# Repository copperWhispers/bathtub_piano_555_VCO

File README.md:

# bathtub_piano_555_VCO
bathtub tune-able analog keyboard based around a 555 timer chip used in PPM configuration.

Story Telling of the journey:
https://youtu.be/zMRLficPjbc

NE555:
https://www.ti.com/lit/ds/symlink/ne555.pdf

KiCAD Schematic and Layout attached.

Also attached a rough notes document which is the doc I wrote into as I designed this circuit, you can see it as an in depth technical version of the journey presented in the video.

References:

Ref1: notes and their frequencies
https://www.idrumtune.com/ultimate-guide-to-musical-frequencies/

Ref2: a complicated VCO + various waveform generators module. +/-12V
https://musicfromouterspace.com/analogsynth_new/VCO20090724REV0/VCO20090724REV0.html

Ref3: The basics of Oscillators and VCOs well explained step by step with circuits to be used +/12V
https://sound-au.com/project162.htm

Ref4: 555 Timer Datasheet.
https://www.ti.com/lit/ds/symlink/na555.pdf?ts=1779184670697&ref_url=https%253A%252F%252Fwww.ti.com%252Fproduct%252FNA555

Ref5: Virtual grounds and examples.
https://tangentsoft.com/elec/vgrounds.html

Ref6: Potentiometers.
https://www.jotrin.com/technology/details/potentiometer-pinout-symbol-wiring-and-working?srsltid=AfmBOorvFBTv3ZwuU9K10ig9qOE0nMZmXfOxQ9t7uRzYsiRLWB0Qjqkc

Ref7: Inverting OPAMP topology.
https://electrosome.com/inverting-amplifier-using-opamp/

Ref8: RMS Formulae:
https://www.electronics-tutorials.ws/accircuits/rms-voltage.html

Ref9: Tim Stinchcomb Tri to SIne.
https://www.timstinchcombe.co.uk/index.php?pge=trisin

Ref10: TI Analog Engineer’s Pocket Reference.
https://www.ti.com/product-category/amplifiers/analog-engineers-pocket-reference-guide.html

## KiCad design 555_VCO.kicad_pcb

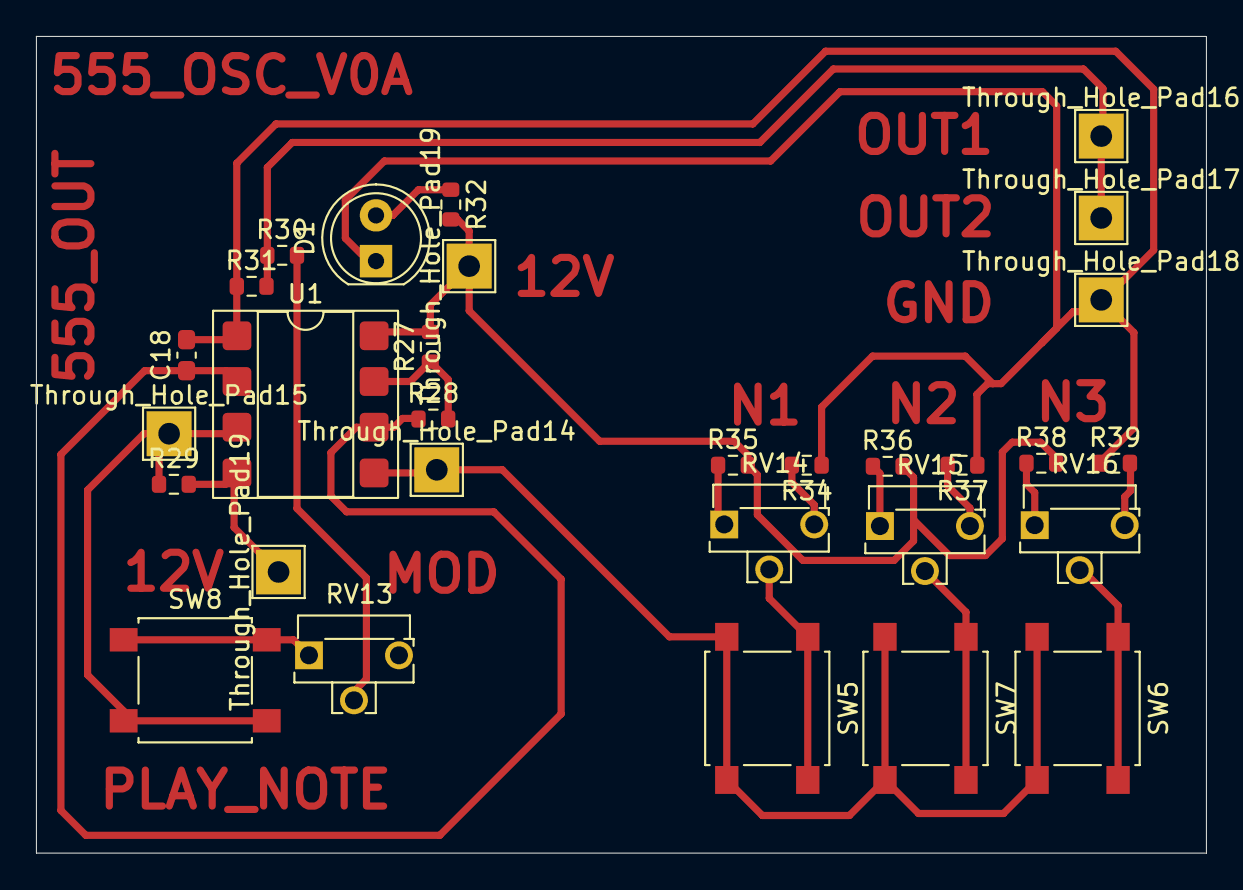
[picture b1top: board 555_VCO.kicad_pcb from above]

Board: 2 copper layers, 65.0 x 45.4 mm, 30 parts (0 on the bottom side), 19 nets.

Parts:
C18: 0.15u; C_0603_1608Metric_Pad1.08x0.95mm_HandSolder
D1: LED; LED_D5.0mm
R27: 27k; R_0603_1608Metric
R28: 10k; R_0603_1608Metric
R29, R32, R34, R37, R39: 1k; R_0603_1608Metric
R30: 1k4; R_0603_1608Metric
R31: 100; R_0603_1608Metric
R35, R36, R38: 2k2; R_0603_1608Metric
RV13: 500k_trim; Potentiometer_Runtron_RM-063_Horizontal
RV14, RV15, RV16: 10k_trim; Potentiometer_Runtron_RM-063_Horizontal
SW5, SW6, SW7, SW8: Push_Button; SW_SPST_B3S-1000
Through_Hole_Pad14, Through_Hole_Pad15, Through_Hole_Pad16, Through_Hole_Pad17, Through_Hole_Pad18, Through_Hole_Pad19, Through_Hole_Pad19#2: TestPoint_THTPad_2.5x2.5mm_Drill1.2mm
U1: NE555P; DIP-8_W7.62mm_SMDSocket_SmallPads

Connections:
/555_OSC_OUT: R29.1, SW8.2, Through_Hole_Pad15.1, U1.3 (OUT)
/AUDIO_AMP_INPUT: R30.1, R31.2, Through_Hole_Pad16.1, Through_Hole_Pad17.1
/MODULATION_INPUT: SW5.2, SW6.2, SW7.2, Through_Hole_Pad14.1, U1.5 (CONT)
GND: C18.2, D1.1, R31.1, R34.1, R37.1, R39.1, Through_Hole_Pad18.1, U1.1 (GND)
unnamed: D1.2, R32.1
unnamed: R30.2, RV13.2
unnamed: R34.2, RV14.3
unnamed: R35.1, RV14.1
unnamed: R36.1, RV15.1
unnamed: R37.2, RV15.3
unnamed: R38.1, RV16.1
unnamed: R39.2, RV16.3
unnamed: RV13.1, SW8.1
unnamed: RV14.2, SW5.1
unnamed: RV15.2, SW7.1
unnamed: RV16.2, SW6.1
unnamed: R27.1, R28.2, U1.7 (DISCH)
unnamed: C18.1, R28.1, U1.2 (TRIG), U1.6 (THRES)
VDD_12V: R27.2, R29.2, R32.2, R35.2, R36.2, R38.2, Through_Hole_Pad19.1, Through_Hole_Pad19#2.1, U1.4 (~RST), U1.8 (VCC)
